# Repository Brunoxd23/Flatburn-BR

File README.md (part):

# FLATBURN: O City Scanner Open-Source (Versão Brasil - Flatburn-BR)

Desenvolvido originalmente no [MIT Senseable City Lab](https://senseable.mit.edu) como parte do projeto [City Scanner](https://senseable.mit.edu/cityscanner/), o **Flatburn** é uma plataforma aberta, modular e movida a energia solar para sensoriamento ambiental urbano instalada em veículos em circulação (ônibus, viaturas, etc.).

Este repositório (**Flatburn-BR**) contém o firmware otimizado, documentação completa em português, esquemáticos de hardware e ferramentas de download de dados para implantação no Brasil.

---

## 📋 Sumário
1. [Especificações Técnicas](#-especificações-técnicas)
2. [Arquitetura do Firmware](#%EF%B8%8F-arquitetura-do-firmware)
3. [Estrutura de Pastas e Módulos](#-estrutura-de-pastas-e-módulos)
4. [Configuração do Ambiente e Ferramentas](#%EF%B8%8F-configuração-do-ambiente-e-ferramentas)
5. [Comandos de Compilação e Gravação (Particle CLI)](#-comandos-de-compilação-e-gravação-particle-cli)
6. [Manual de Comandos do Firmware (CLI Serial / Nuvem)](#-manual-de-comandos-do-firmware-cli-serial--nuvem)
7. [Configurações Principais (cityscanner_config.h)](#-configurações-principais-cityscanner_configh)
8. [Estrutura dos Payloads de Dados](#-estrutura-dos-payloads-de-dados)
9. [Tratamento de Data, Hora e Fuso Horário (Brasília UTC-3)](#-tratamento-de-data-hora-e-fuso-horário-brasília-utc-3)
10. [Histórico de Alterações e Correções de Estabilidade](#%EF%B8%8F-histórico-de-alterações-e-correções-de-estabilidade)

---

## ⚙️ Especificações Técnicas

- **Microcontrolador / Módulo IoT:** Particle B-Series SoM (`b5som` / `bsom`) com suporte a rede celular LTE.
- **Versão do Sistema Operacional:** [Particle Device OS @ 6.3.4](https://docs.particle.io/reference/device-os/firmware/).
- **Linguagem:** C++ (Particle Wiring API).
- **Sensores Embarcados:**
  - **Qualidade do Ar (Material Particulado):** Sensirion SPS30 (PM1.0, PM2.5, PM4, PM10).
  - **Meteorologia:** BME280 (Temperatura, Umidade e Pressão).
  - **Gases:** Sensor eletroquímico via conversor ADC de alta resolução (ADS1256).
  - **Ruído Urbano:** Microfone analógico com amostragem contínua.
  - **Geolocalização:** Módulo GPS com saída NMEA.
  - **Movimento e Detecção de Inatividade:** Acelerômetro / IMU.
  - **Telemetria de Bateria e Solar:** Medidores BQ24195 e LC709203F.
  - **Armazenamento Local:** Módulo MicroSD (buffer redundante quando sem conexão).

---

## 🏛️ Arquitetura do Firmware

O firmware adota um padrão modular de classes Singleton, onde cada classe é responsável por um subsistema do dispositivo:

| Módulo / Classe | Arquivos | Responsabilidade |
| :--- | :--- | :--- |
| **Cityscanner** | `firmware/src/cityscanner.h / .cpp` | Gerenciador central. Controla o loop principal e máquina de estados (`IDLE`, `REALTIME`, `LOGGING`, `PWRSAVE`). |
| **CitySense** | `firmware/src/cityscanner_sense.h / .cpp` | Inicialização, amostragem e conversão de dados de todos os sensores ambientais (SPS30, BME280, ADS1256, Ruído). |
| **CityVitals** | `firmware/src/cityscanner_vitals.h / .cpp` | Aquisição de dados de diagnóstico elétrico: nível de bateria (SOC), tensão, corrente, temperatura e produção de energia dos painéis solares. |
| **CityStore** | `firmware/src/cityscanner_store.h / .cpp` | Manipulação do cartão MicroSD: gravação em buffer CSV, rotação de arquivos e descarga de dados via USB. |
| **LocationService** | `firmware/src/location_service.h / .cpp` | Leitura e parsing de mensagens NMEA do GPS (latitude, longitude, velocidade, altitude e horário Epoch). |
| **MotionService** | `firmware/src/motion_service.h / .cpp` | Monitora o acelerômetro. Se o veículo ficar parado por mais de `INACTIVITY_TIME`, ativa rotinas de economia de energia. |
| **CitySleep** | `firmware/src/cityscanner_sleep.h / .cpp` | Controle de modos de suspensão (`Stop`, `Hibernate`, `Light Sleep`) para evitar descarregar a bateria durante a noite ou estacionado. |
| **CS_core** | Em `cscore` (lib) | Controle dos reguladores de tensão (chaveamento dos barramentos 3.3V e 5V dos sensores). |
| **CLI Handler** | `firmware/src/cityscanner_cli.h` | Interpretador de comandos que recebe instruções via porta Serial (USB) ou pela função de nuvem da Particle. |

---

## 📁 Estrutura de Pastas e Módulos

```text
flartBurn/
├── README.md                  # Documentação principal no GitHub (Português)
├── LICENSE                    # Licença MIT
├── firmware/                  # Código fonte do microcontrolador
│   ├── project.properties     # Configuração básica do projeto Particle
│   ├── README.md              # Documentação técnica do firmware
│   ├── README.pt-BR.md        # Documentação completa em português
│   ├── src/                   # Arquivos-fonte (.cpp e .h)
│   └── lib/                   # Bibliotecas dos sensores e periféricos
├── hardware/                  # Esquemáticos elétricos, PCB (KiCad) e modelos CAD/3D (STEP/STL)
└── documentation/             # Site de documentação Docusaurus e ferramentas (flatburn_downloader.html)
```

---

## 🛠️ Configuração do Ambiente e Ferramentas

Para trabalhar com este firmware, você só precisa do **Node.js** e do **Particle CLI** instalados no computador.

### 1. Instalar o Particle CLI (Global)
No terminal do seu computador (PowerShell ou Prompt de Comando):
```bash
npm install -g particle-cli
```

### 2. Verificar a Instalação
```bash
particle --version
# Exemplo de saída: 3.51.0
```

### 3. Fazer Login na Conta Particle
Para utilizar o compilador na nuvem e os recursos remotos:
```bash
particle login
```
*Insira seu e-mail e senha cadastrados no console da [Particle.io](https://login.particle.io).*

---

## 🚀 Comandos de Compilação e Gravação (Particle CLI)

Todos os comandos abaixo devem ser executados a partir da raiz do repositório (`flartBurn/`):

### 1. Binários Pré-compilados Prontos para Teste
Para facilitar testes imediatos em bancada ou em campo, o projeto dispõe de dois binários prontos:

| Arquivo `.bin` | Configuração Celular | Comportamento do LED | Uso Recomendado |
| :--- | :--- | :--- | :--- |
| **`firmware_sem_celular.bin`** | `CELLULAR_ON_STARTUP FALSE` | ⚪ **Branco suave** (offline) | **Bancada e desenvolvimento local:** Desativa o modem na inicialização, liberando a Serial instantaneamente e gravando dados no MicroSD. |
| **`firmware_com_celular.bin`** | `CELLULAR_ON_STARTUP TRUE` | 🟢 **Verde** $\rightarrow$ 🌐 **Ciano** | **Operação em campo com telemetria:** Conecta à rede móvel e envia dados para a Nuvem Particle. |

---

### 2. Automação com Scripts Rápidos (.bat no Windows)
Você pode executar as ações com 2 cliques ou pelo terminal:

- **Compilação Automática:**
  - `compilar_sem_celular.bat` $\rightarrow$ Ajusta a configuração para `FALSE` e compila `firmware_sem_celular.bin`.
  - `compilar_com_celular.bat` $\rightarrow$ Ajusta a configuração para `TRUE` e compila `firmware_com_celular.bin`.
- **Gravação Direta via USB:**
  - `gravar_sem_celular.bat` $\rightarrow$ Grava a versão offline via USB.
  - `gravar_com_celular.bat` $\rightarrow$ Grava a versão online via USB.

---

### 3. Gravar no Dispositivo via USB (Cabo)
1. Conecte a placa ao computador pelo cabo USB.
2. Coloque a placa em **modo DFU**:
   - Mantenha pressionados os botões **RESET** e **MODE**.
   - Solte o botão **RESET** e continue segurando o botão **MODE** até o LED RGB começar a **piscar rápido em amarelo / âmbar**.
   - Solte o botão **MODE**.
3. Execute o comando de gravação da versão desejada:
   ```bash
   # Opção A: Versão Offline (Recomendada para testes e sem antena celular)
   particle flash --usb firmware_sem_celular.bin

   # Opção B: Versão Online (Conexão celular ativa)
   particle flash --usb firmware_com_celular.bin
   ```

---

### 4. Compilar Manualmente via Terminal
Caso altere o código-fonte manualmente e queira compilar via linha de comando:
```bash
particle compile b5som firmware/ --target 6.3.4 --saveTo firmware.bin
```

---

### 5. Gravar no Dispositivo via Nuvem (OTA - Sem cabo)
Caso o dispositivo esteja na rua ou conectado via celular:
```bash
particle flash NOME_OU_ID_DO_DISPOSITIVO firmware.bin
```

### 6. Visualizar Logs da Porta Serial (Monitor em Tempo Real)
Para acompanhar leituras de sensores e mensagens de debug enviadas pelo dispositivo via USB:
```bash
particle serial monitor --follow
```

### 7. Listar Dispositivos Conectados na USB
```bash
particle serial list
```

### 8. Como Baixar e Unificar o CSV de Dados via Navegador
Para descarregar todos os dados gravados no cartão MicroSD e gerar uma planilha única `.csv` com georreferenciamento e timestamps corrigidos:

1. **Liberar a porta USB:**  
   Se o comando `particle serial monitor` estiver rodando no terminal, feche-o pressionando **`Ctrl + C`** *(no Windows, a porta serial fica bloqueada caso outro programa esteja usando)*.
2. **Abrir a ferramenta web:**  
   Abra o arquivo [`documentation/content/explore/flatburn_downloader.html`](documentation/content/explore/flatburn_downloader.html) no **Google Chrome** ou **Microsoft Edge** (estes navegadores possuem suporte nativo à *Web Serial API*).
3. **Conectar ao dispositivo:**  
   Na página aberta, clique em **Connect** e selecione a porta serial do Flatburn (geralmente identificada como **"B-SoM CDC Mode"** ou **"USB Serial Device"**).
4. **Baixar e Unificar:**  
   Clique no botão **"Download All, Parse & Merge"**. O sistema baixa todos os blocos do SD, limpa os dados e unifica tudo em uma única tabela.
5. **Salvar o arquivo:**  
   Clique em **"Save CSV File"** para salvar a planilha `.csv` final na sua pasta de Downloads.

### 9. Significado dos LEDs de Status (Guia de Cores)
O módulo Particle e a placa Flatburn utilizam LEDs indicadores para sinalizar o estado do hardware e das conexões:

| Cor do LED | Padrão | Significado | O que fazer / Situação |
| :--- | :--- | :--- | :--- |
| 🟢 **Verde** | Piscando rápido | **Buscando Rede Celular:** O modem celular está ativo e tentando se registrar na torre de telefonia. | Comportamento normal logo após ligar a placa ou gravar novo firmware. |
| 🔵 **Azul Escuro** | Piscando | **Modo de Escuta (Listening Mode):** Placa aguardando comandos USB ou sistema desatualizado (firmware do Flatburn pausado). | 1. Dê 1 clique no botão **RESET**.<br>2. Se continuar azul ou for placa nova, coloque em DFU (amarelo) e execute `particle update`. |
| 🌐 **Ciano (Azul Claro)** | Piscando rápido | **Conectando à Nuvem:** Autenticando com os servidores da Particle após conectar na torre celular. | Aguardar alguns segundos até a conclusão do handshake. |
| 🌐 **Ciano (Azul Claro)** | Pulsando suave ("respirando") | **Conectado e Online:** Comunicação ativa e estável com a Nuvem Particle. | Dispositivo 100% online e apto a transmitir dados em tempo real. |
| 🟡 **Amarelo / Âmbar** | Piscando rápido | **Modo DFU:** Placa pronta para receber novo firmware via USB (`particle flash --usb`). | Gravar o firmware pelo terminal ou pressionar RESET para sair. |
| ⚪ **Branco** | Pulsando suave | **Modo Offline:** Modem celular desligado (`Cellular.off()`), gravando dados apenas localmente no SD Card. | Padrão do Flatburn para economia de energia durante coletas. |
| 🟣 **Magenta / Roxo** | Piscando rápido | **Safe Mode / Atualização OTA:** Atualizando firmware pela nuvem ou em modo de proteção. | Aguardar o término do download/gravação. |
| 🔴 **Vermelho** *(Placa Flatburn)* | Piscando lento / Aceso | **Carga / Sistema Ativo:** LED do circuito de alimentação (BQ25798) e amostragem ativa dos sensores. | Normal durante a operação e quando conectado ao cabo USB. |

> [!TIP]
> **Placa travada piscando em Azul Escuro (Listening Mode) ou não inicializa após gravar?**  
> Isso é muito comum em placas novas ou virgens de fábrica cujo sistema operacional interno (*Device OS*) ainda está em versões antigas:
> 1. Feche o monitor serial com `Ctrl + C` para liberar a porta USB.
> 2. Coloque a placa em **modo DFU** (LED piscando rápido em **amarelo**): segure `RESET + MODE`, solte `RESET`, espere piscar em amarelo e solte `MODE`.
> 3. No terminal, execute a atualização do sistema:
>    ```bash
>    particle update
>    ```
> 4. Após a conclusão com sucesso, regrave o firmware desejado (`particle flash --usb firmware_sem_celular.bin` ou use o script `.bat`).

---

## 🎮 Manual de Comandos do Firmware (CLI Serial / Nuvem)

O firmware possui um interpretador de comandos integrado (`cityscanner_cli.h`).  
Os comandos podem ser enviados de duas formas:
1. **Pela porta Serial USB:** digitando diretamente no monitor serial ou enviando via scripts em Python.
2. **Pela Nuvem da Particle:** chamando a função `CLI` da placa pelo terminal:
   ```bash
   particle call NOME_DO_DISPOSITIVO CLI "COMANDO"
   ```

Abaixo está a lista completa de comandos suportados:

### A. Download e Gerenciamento do Cartão SD
| Comando | Descrição |
| :--- | :--- |
| `LIST` | Lista todos os arquivos `.csv` armazenados no cartão MicroSD. |
| `READ:<nome_arquivo>` | Imprime na Serial todo o conteúdo do arquivo especificado (ex: `READ:0001.csv`). |
| `DELETE_ALL` | Remove do cartão SD os arquivos que já foram baixados. |
| `sd,dump,all` | Despeja todos os arquivos de dados na porta Serial. |
| `sd,dump,<N>` | Despeja os últimos `<N>` arquivos de dados (ex: `sd,dump,5`). |
| `sd,files` | Retorna a quantidade de arquivos de dados pendentes no cartão SD. |
| `sd,health` | Retorna o status de saúde e conectividade do cartão SD. |
| `sd,reinit` | Reinicializa o driver do cartão SD caso ocorra alguma falha. |
| `sd,format` | Formata e reinicia a estrutura de pastas do cartão SD. |

### B. Leituras Imediatas e Sensores
| Comando | Descrição |
| :--- | :--- |
| `last,payload` | Retorna a última leitura completa dos sensores (GPS + Poluentes + Clima). |
| `last,vitals` | Retorna a última leitura de telemetria elétrica (Bateria + Solar). |
| `device-check` | Executa um teste em todos os sensores e retorna a linha consolidada. |
| `location` | Retorna as coordenadas GPS atuais (`latitude,longitude`). |
| `battery` | Retorna status detalhado da bateria (SOC %, tensão, corrente de carga). |
| `solar` ou `input` | Retorna a tensão e corrente produzidas pelos painéis solares. |
| `opc` | Retorna os dados brutos da última leitura do sensor de material particulado SPS30. |

### C. Controle de Energia dos Sensores (Chaveamento de Barramentos)
| Comando | Descrição |
| :--- | :--- |
| `3v3on` | Liga a alimentação de 3.3V e inicializa GPS, temperatura, ruído e gás. |
| `3v3off` | Desliga todos os sensores de 3.3V para economizar energia. |
| `5von` | Liga a linha de 5V (alimentação necessária para o sensor SPS30). |
| `5voff` | Desliga a linha de 5V e desativa o sensor SPS30. |
| `opcon` | Liga o sensor de partículas SPS30. |
| `opcoff` | Desliga o sensor de partículas SPS30. |
| `autosleep,on` | Habilita o modo de suspensão automática quando o veículo estaciona. |
| `autosleep,off` | Força o dispositivo a ficar acordado mesmo se estiver parado. |

### D. Controle do Sistema e Modos de Espera
| Comando | Descrição |
| :--- | :--- |
| `reboot` | Reinicia o microcontrolador imediatamente (`System.reset()`). |
| `dfu` | Coloca a placa em modo DFU remotamente para receber novo firmware. |
| `stop` | Coloca a placa em modo de espera profundo (Stop Sleep) por até 12 horas ou até movimento. |
| `hibernate,<tempo>,<unidade>` | Coloca a placa em hibernação profunda por um tempo pré-determinado.<br>Exemplo: `hibernate,30,minutes` ou `hibernate,2,hours`. |

---

## ⚙️ Configurações Principais (`cityscanner_config.h`)

Para alterar a frequência de coleta, modos de operação ou limites de segurança de bateria, edite o arquivo [firmware/src/cityscanner_config.h](firmware/src/cityscanner_config.h):

| Parâmetro | Padrão | O que configura |
| :--- | :--- | :--- |
| `MODE` | `LOGGING` | Modo padrão de operação (`REALTIME`, `LOGGING` ou `PWRSAVE`). |
| `SAMPLE_RATE` | `5` | Intervalo em segundos entre amostragens de sensores de qualidade do ar. |
| `VITALS_RATE` | `300` | Intervalo em segundos (5 minutos) entre leituras de telemetria da bateria/solar. |
| `INACTIVITY_TIME`| `120` | Segundos sem movimento do veículo para ativar o modo de economia. |
| `AUTOSLEEP` | `TRUE` | Ativa/desativa se a placa dorme automaticamente quando estacionada. |
| `LOW_BATTERY_THRESHOLD` | `3.70` | Tensão em Volts da bateria para acionar o alerta de bateria baixa. |
| `RECORDS_PER_FILE` | `200` | Quantidade de registros por arquivo `.csv` no cartão SD antes de rotacionar. |
| `CELLULAR_ON_STARTUP` | `FALSE` | Define se a conexão celular é ligada imediatamente ao dar boot. |
| `TIMEZONE_OFFSET` | `-3` | Fuso horário em horas (padrão `-3` para Horário de Brasília / São Paulo). |

---

## 📊 Estrutura dos Payloads de Dados

Os dados gravados no cartão SD e transmitidos via nuvem/USB seguem o padrão CSV delimitado por vírgulas:

### 1. Payload de Sensores (Ambiental)
```text
deviceID, timestamp, latitude, longitude, PM1.0, PM2.5, PM4, PM10, numPM0.5, numPM1, numPM2.5, numPM4, numPM10, PM_size, temperature, humidity, gas_op1_w, gas_op1_r, gas_op2_w, gas_op2_r, noise
```

### 2. Payload de Vitals (Diagnóstico Elétrico)
```text
deviceID, time, latitude, longitude, SOC_batt, temp_batt, voltage_batt, voltage_particle, current_batt, isCharging, isCharginS, temp_int, hum_int, voltage_solar, current_solar, cell_strength
```

---

## 🕒 Tratamento de Data, Hora e Fuso Horário (Brasília UTC-3)

Para garantir precisão nas análises em **São Paulo / Brasil**, o firmware conta com as seguintes regras de sincronização temporal e georreferenciamento:

### 1. Correção do Timestamp Epoch
- O cálculo da data do GPS utiliza `CalendarYrToTm(tinyGps->date.year())`, convertendo o ano civil de 4 dígitos (ex.: 2024, 2026) diretamente em anos transcorridos desde 1970.
- Isso gera um **Unix Epoch UTC padronizado em segundos** na coluna `timestamp` do CSV, pronto para ser lido pelo downloader web ou bibliotecas de análise (ex.: Pandas).

### 2. Sincronização Automática do Relógio Interno (RTC)
- Assim que o módulo GPS obtém uma data e hora válidas dos satélites (`tinyGps->date.isValid()` e ano >= 2020), o firmware executa `Time.setTime(epoch)`.

### 3. Fuso Horário de Brasília (`TIMEZONE_OFFSET -3`)
- O parâmetro `#define TIMEZONE_OFFSET -3` no [cityscanner_config.h](firmware/src/cityscanner_config.h) ativa a compensação local via `Time.zone(-3)`. Os arquivos no SD são nomeados como `MMDDHHMM.csv` em horário de Brasília.

---

## 🛠️ Histórico de Alterações e Correções de Estabilidade

1. **Taxa de Transmissão Serial Atualizada para 115200 Baud:**
   - A inicialização da porta Serial em [main.cpp](firmware/src/main.cpp) foi ajustada de `9600` para `115200` baud. Isso sincronizou a velocidade do microcontrolador com a interface web ([flatburn_downloader.html](documentation/content/explore/flatburn_downloader.html)), permitindo o download ultrarrápido dos arquivos do cartão SD via USB.

2. **Timeout de Proteção no Conversor ADC ADS1256:**
   - Adicionada verificação com timeout de 100ms nas funções `waitForLowDRDY()` e `waitForHighDRDY()` no driver do sensor de gás ADS1256 ([ADS1256.cpp](firmware/lib/ADS1256-main/src/ADS1256.cpp)). Evita travamentos caso o sensor esteja ausente ou o pino DRDY em nível alto.

3. **Correção na Ordem de Energização das Linhas 3.3V e 5V:**
   - Em [cityscanner.cpp](firmware/src/cityscanner.cpp), a inicialização dos barramentos de alimentação (`core.enable3V3(true)` e `core.enable5V(true)`) foi movida para o **início da função `init()`**, garantindo energia no barramento I2C e SD Card antes do acesso.

4. **Desativação de Sketches de Exemplo nas Bibliotecas (`.ino.bak`):**
   - Todos os arquivos `.ino` situados dentro da pasta `lib/` (ex.: `ADS1256-Example.ino`) foram renomeados para `.ino.bak`. Evita que o compilador da Particle inclua sketches de teste de bibliotecas no binário final (~80 KB).

5. **Exibição do Modo `LOGGING` em Tempo Real na Serial:**
   - Ativada a chamada da função `printDebug()` no bloco `case LOGGING:` dentro do `loop()`, imprimindo a tabela consolidada de todos os sensores diretamente no monitor serial a cada 5 segundos.

6. **Desativação Total do Modem Celular no Boot:**
   - Incluído o comando `Cellular.off()` no bloco `STARTUP()` de [main.cpp](firmware/src/main.cpp) para eliminar a busca por torres e o LED piscando em verde.

7. **Correção do Pino CS e Barramento SPI1 do Conversor ADC de Gases (ADS1256):**
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
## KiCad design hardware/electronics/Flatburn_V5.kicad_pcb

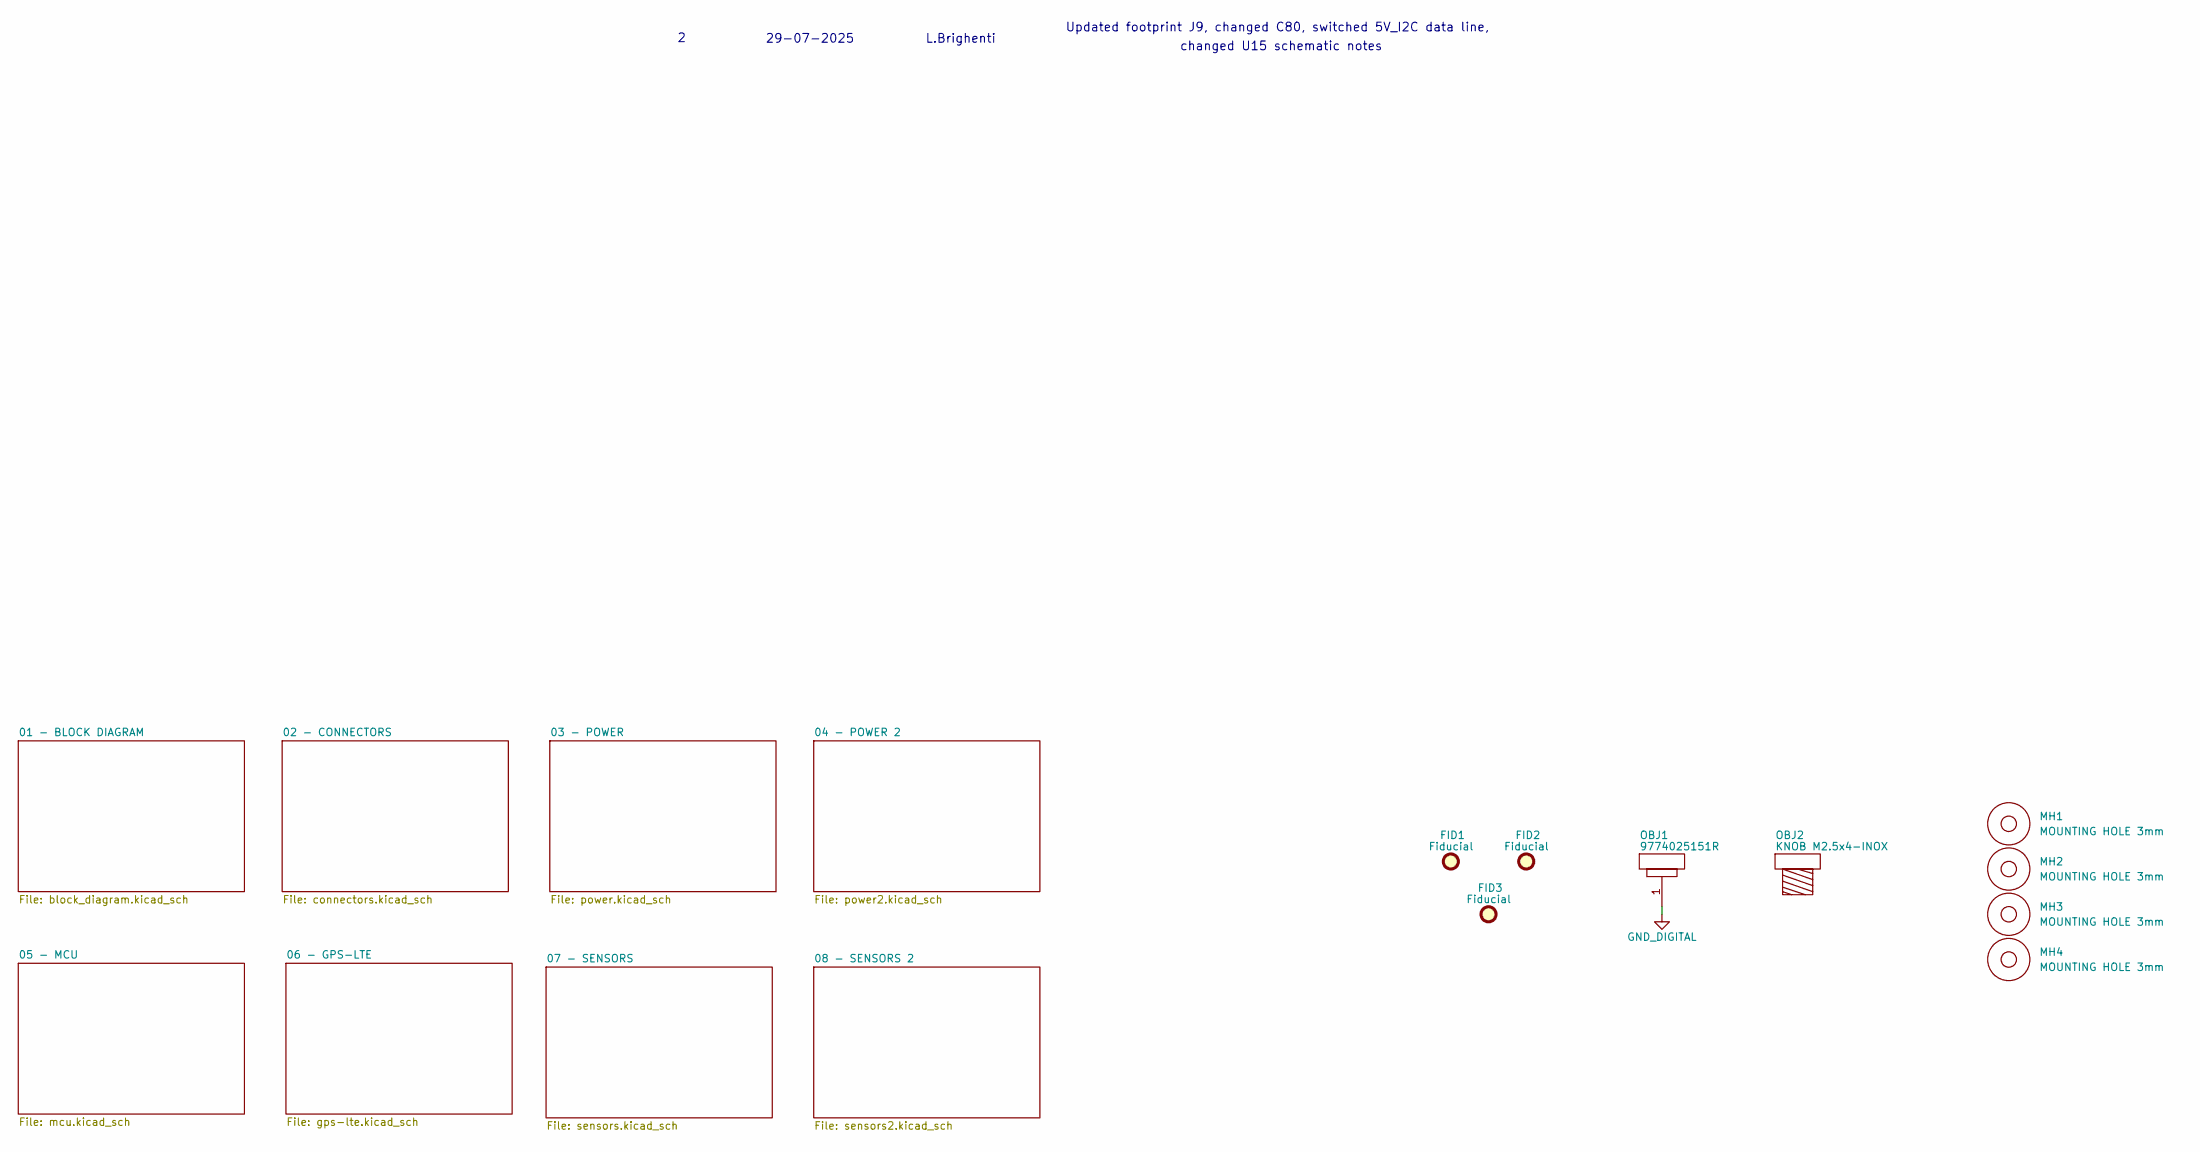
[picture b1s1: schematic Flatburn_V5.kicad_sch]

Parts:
FID1, FID2, FID3: Fiducial; Fiducial_1mm_Mask3mm
MH1, MH2, MH3, MH4: MOUNTING HOLE 3mm
OBJ1: 9774025151R; SPACER M2.5 - 9774025151R; MPN 9774025151R
OBJ2: KNOB M2.5x4-INOX

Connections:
GND_DIGITAL: OBJ1.1; also elsewhere on the board

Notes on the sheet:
L.Brighenti
Updated footprint J9, changed C80, switched 5V_I2C data line,
29-07-2025
changed U15 schematic notes

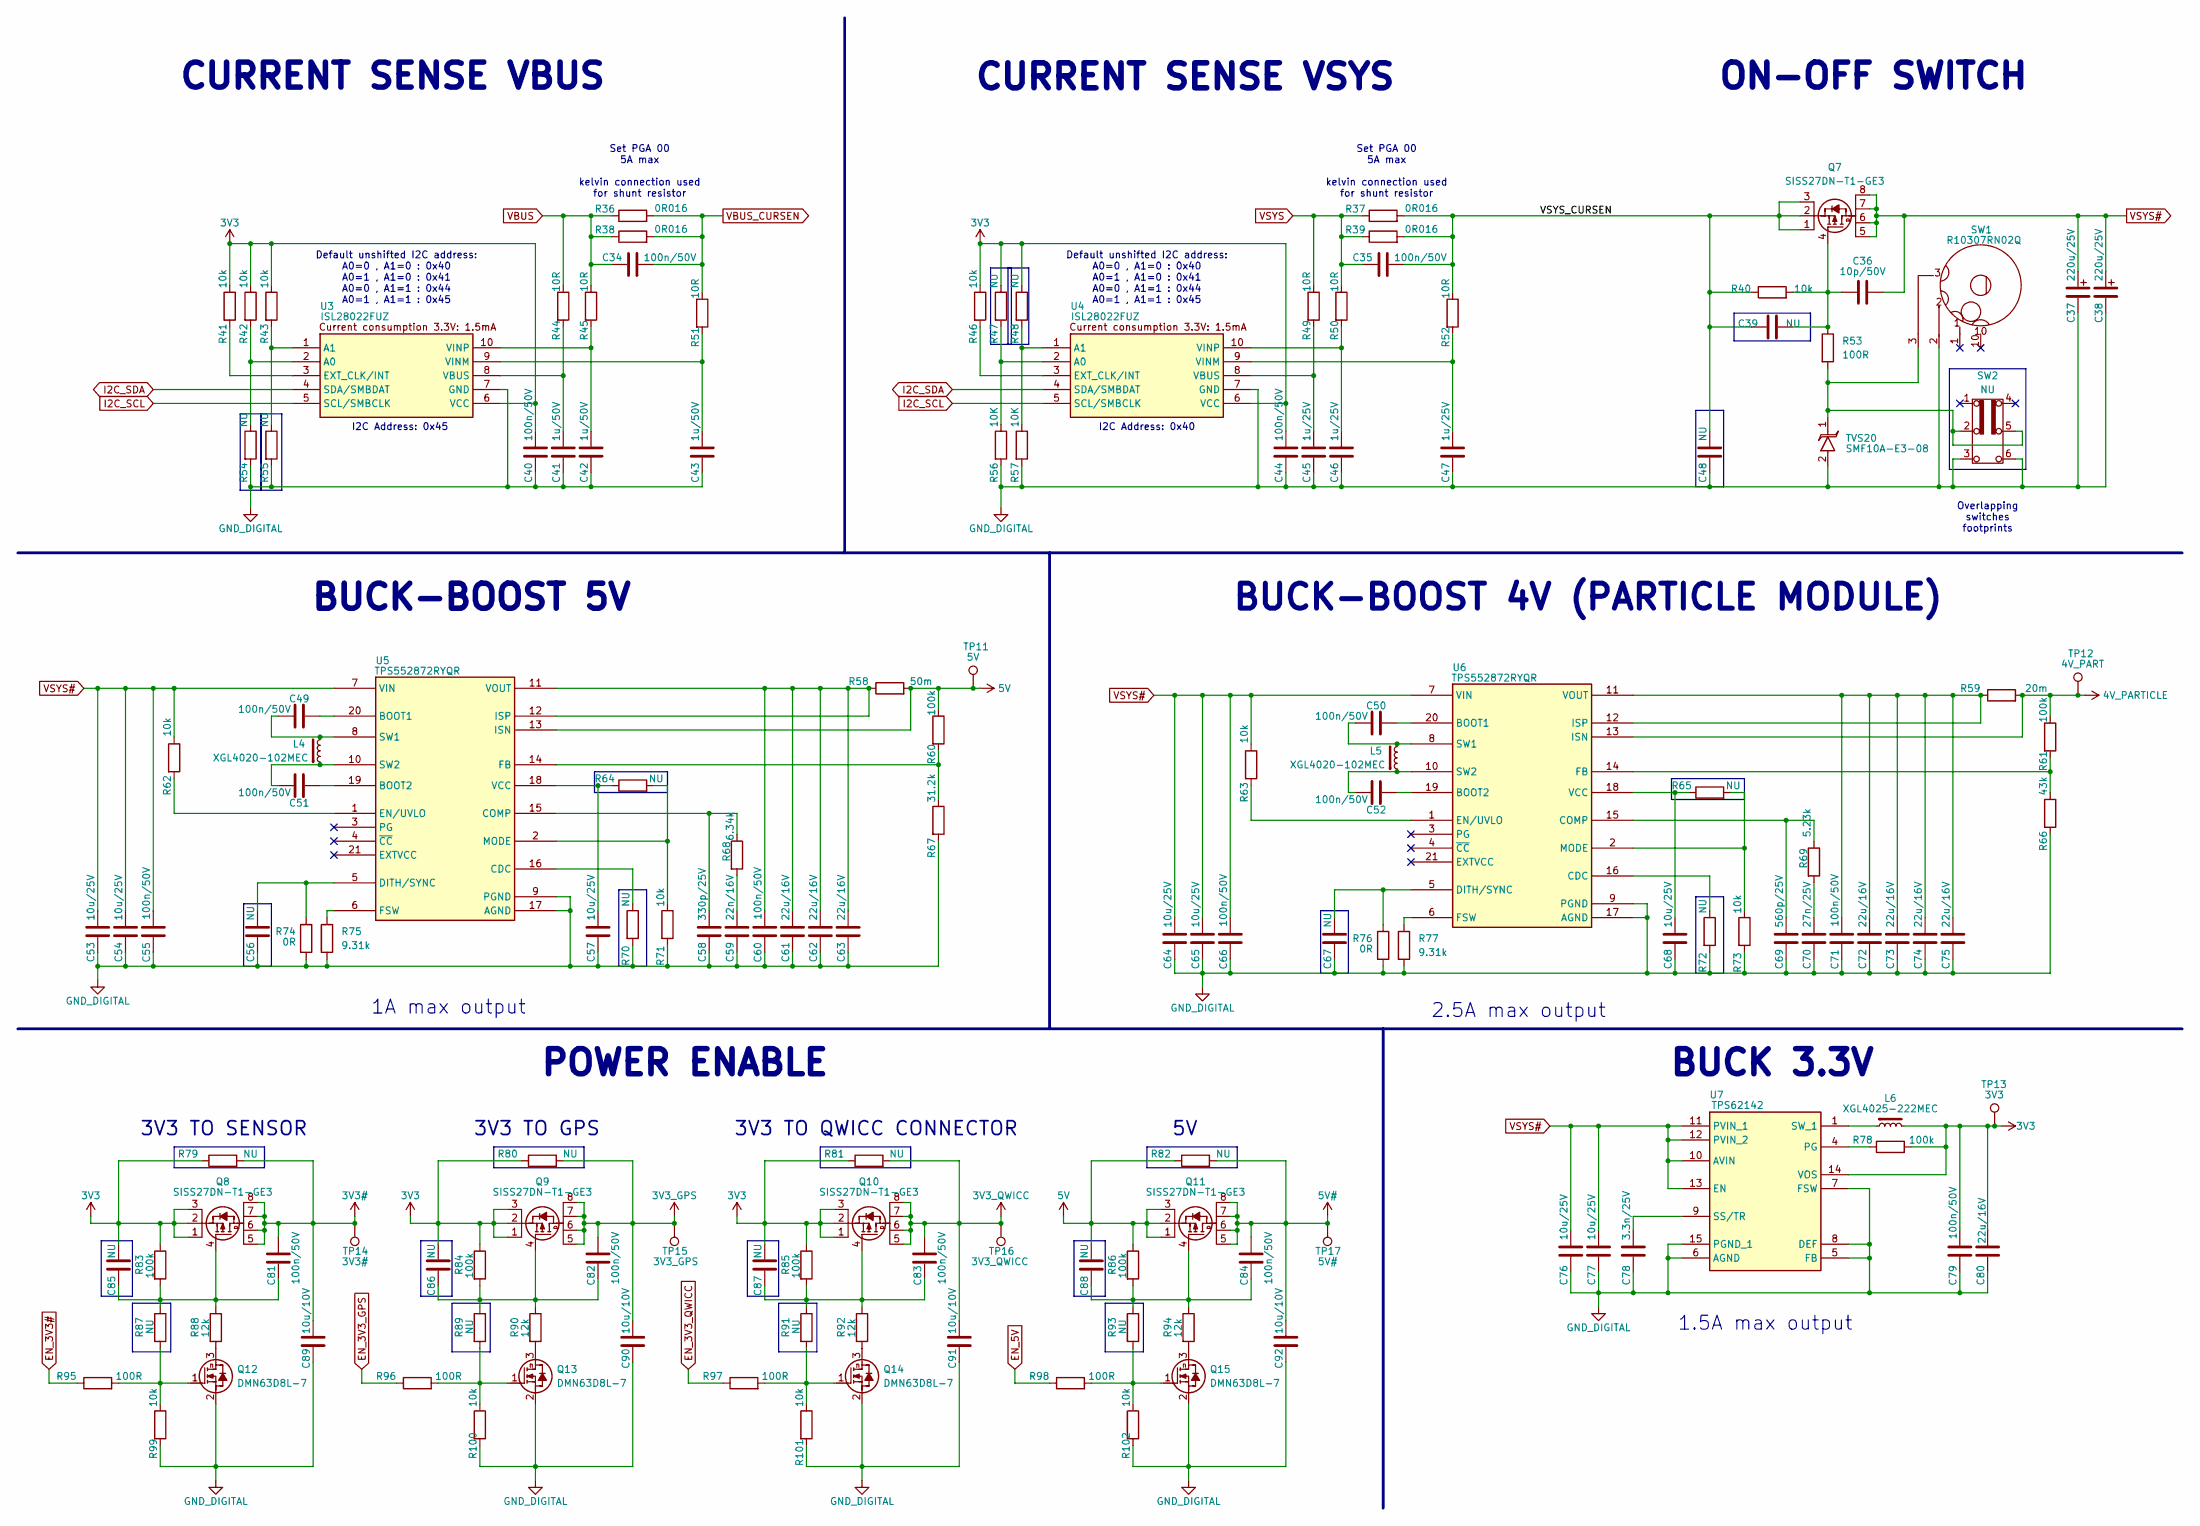
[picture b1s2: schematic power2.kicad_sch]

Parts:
C34, C35, C40, C44, C49, C50, C51, C52, C55, C60, C66, C71, C79, C81, C82, C83, C84: 100n/50V; C_0402_1005Metric
C36: 10p/50V; C_0402_1005Metric; MPN GCM1555C1H100JA16D
C37, C38: 220u/25V; CP_Elec_6.3x7.7; MPN UCM1E221MCL1GS
C39, C48, C85, C86, C87, C88: NU; C_0402_1005Metric
C41, C42, C43: 1u/50V; C_0805_2012Metric
C45, C46, C47: 1u/25V; C_0603_1608Metric; MPN CL10B105KA8NNNC
C53, C54, C57, C64, C65, C68, C76, C77: 10u/25V; C_0603_1608Metric; MPN GRM188R61E106KA73D
C56, C67: NU; C_0603_1608Metric; MPN GRM188R61E106KA73D
C58: 330p/25V; C_0603_1608Metric; MPN C0603C331J3HACAUTO
C59: 22n/16V; C_0603_1608Metric; MPN 0603YC223J4T2A
C61, C62, C63, C72, C73, C74, C75: 22u/16V; C_0805_2012Metric; MPN GRM21BC81C226ME44L
C69: 560p/25V; C_0603_1608Metric; MPN GRM1885C1E561JA01D
C70: 27n/25V; C_0603_1608Metric; MPN C0603C273J3RACAUTO
C78: 3.3n/25V; C_0402_1005Metric; MPN 885012205047
C80: 22u/16V; C_0603_1608Metric; MPN KGM15CR51C226MT
C89, C90, C91, C92: 10u/10V; C_0603_1608Metric
L4, L5: XGL4020-102MEC; L_Coilcraft_XxL4020; MPN XGL4020-102MEC
L6: XGL4025-222MEC; L_Coilcraft_XxL4020; MPN XGL4025-222MEC
Q7, Q8, Q9, Q10, Q11: SISS27DN-T1-GE3; PowerPAK 121-8; MPN SISS27DN-T1-GE3
Q12, Q13, Q14, Q15: DMN63D8L-7; SOT-23; MPN DMN63D8L-7
R36, R37, R38, R39: 0R016; R_1206_3216Metric; MPN RL1206FR-070R016L
R40, R41, R42, R43, R46, R62, R63, R71, R73, R99, R100, R101, R102: 10k; R_0402_1005Metric
R44, R45, R49, R50, R51, R52: 10R; R_0603_1608Metric
R47, R48, R54, R55, R64, R65, R70, R72: NU; R_0402_1005Metric
R53, R95, R96, R97, R98: 100R; R_0402_1005Metric
R56, R57: 10K; R_0402_1005Metric
R58: 50m; R_0603_1608Metric; MPN PE0603FRF570R05L
R59: 20m; R_0603_1608Metric; MPN CFN0603-FZ-R020ELF
R60, R61, R78, R83, R84, R85, R86: 100k; R_0402_1005Metric
R66: 43k; R_0402_1005Metric; MPN RC0402FR-0743KL
R67: 31.2k; R_0402_1005Metric; MPN RN73H1ETTP3122D25
R68: 6.34k; R_0603_1608Metric; MPN RR0816P-6341-D-78H
R69: 5.23k; R_0603_1608Metric; MPN CPF0603F5K23C1
R74, R76: 0R; R_0402_1005Metric; MPN RCS04020000Z0ED
R75, R77: 9.31k; R_0402_1005Metric; MPN RC0402FR-079K31L
R79, R80, R81, R82: NU; R_1206_3216Metric; MPN RCA12060000ZSEA
R87, R89, R91, R93: NU; R_0402_1005Metric; MPN RCS04020000Z0ED
R88, R90, R92, R94: 12k; R_0402_1005Metric
SW1: R10307RN02Q; MPN R10307RN02Q
SW2: NU; FS22ABP; MPN FS22ABP
TP11: 5V; TestPoint_Pad_D1.0mm
TP12: 4V_PART; TestPoint_Pad_D1.0mm
TP13: 3V3; TestPoint_Pad_D1.0mm
TP14: 3V3#; TestPoint_Pad_D1.0mm
TP15: 3V3_GPS; TestPoint_Pad_D1.0mm
TP16: 3V3_QWICC; TestPoint_Pad_D1.0mm
TP17: 5V#; TestPoint_Pad_D1.0mm
TVS20: SMF10A-E3-08; D_SMF; MPN SMF10A-E3-08
U3, U4: ISL28022FUZ; SOP50P490X110-10N; MPN ISL28022FUZ
U5, U6: TPS552872RYQR; TPS552892QWRYQRQ1; MPN TPS630702RNMR
U7: TPS62142; QFN50P300X300X100-17N-D; MPN TPS62142RGTT

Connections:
3V3: C40.1, C44.1, C79.2, C80.1, C85.2, C86.2, C87.2, L6.1, Q8.1 (S), Q8.2 (S), Q8.3 (S), Q9.1 (S), Q9.2 (S), Q9.3 (S), Q10.1 (S), Q10.2 (S), Q10.3 (S), R41.1, R42.1, R43.1, R46.1, R47.1, R48.1, R78.2, R79.1, R80.1, R81.1, R83.1, R84.1, R85.1, TP13.1, U3.6 (VCC), U4.6 (VCC), U7.14 (VOS); also elsewhere on the board
3V3#: C81.2, C89.1, Q8.5 (D), Q8.6 (D), Q8.7 (D), Q8.8 (D), Q8.9 (D), R79.2, TP14.1; also elsewhere on the board
3V3_GPS: C82.2, C90.1, Q9.5 (D), Q9.6 (D), Q9.7 (D), Q9.8 (D), Q9.9 (D), R80.2, TP15.1; also elsewhere on the board
3V3_QWICC: C83.2, C91.1, Q10.5 (D), Q10.6 (D), Q10.7 (D), Q10.8 (D), Q10.9 (D), R81.2, TP16.1; also elsewhere on the board
4V_PARTICLE: R59.2, R61.1, TP12.1, U6.13 (ISN); also elsewhere on the board
5V: C88.2, Q11.1 (S), Q11.2 (S), Q11.3 (S), R58.2, R60.1, R82.1, R86.1, TP11.1, U5.13 (ISN); also elsewhere on the board
5V#: C84.2, C92.1, Q11.5 (D), Q11.6 (D), Q11.7 (D), Q11.8 (D), Q11.9 (D), R82.2, TP17.1; also elsewhere on the board
/04 - POWER 2/VSYS_CURSEN: C35.1, C39.1, C48.1, Q7.1 (S), Q7.2 (S), Q7.3 (S), R37.2, R39.2, R40.1, R52.1
EN_3V3#: R95.1; also elsewhere on the board
EN_3V3_GPS: R96.1; also elsewhere on the board
EN_3V3_QWICC: R97.1; also elsewhere on the board
EN_5V: R98.1; also elsewhere on the board
GND_DIGITAL: C37.2, C38.2, C40.2, C41.2, C42.2, C43.2, C44.2, C45.2, C46.2, C47.2, C48.2, C53.2, C54.2, C55.1, C56.2, C57.2, C58.2, C59.2, C60.1, C61.2, C62.2, C63.2, C64.2, C65.2, C66.1, C67.2, C68.2, C69.2, C70.2, C71.1, C72.2, C73.2, C74.2, C75.2, C76.2, C77.2, C78.2, C79.1, C80.2, C89.2, C90.2, C91.2, C92.2, Q12.2 (S), Q13.2 (S), Q14.2 (S), Q15.2 (S), R54.2, R55.2, R56.2, R57.2, R66.2, R67.2, R70.2, R71.2, R72.2, R73.2, R74.2, R75.2, R76.2, R77.2, R99.2, R100.2, R101.2, R102.2, SW1.2, SW2.3 (B1), SW2.6 (B2), TVS20.2, U3.7 (GND), U4.7 (GND), U5.9 (PGND), U5.17 (AGND), U6.9 (PGND), U6.17 (AGND), U7.5 (FB), U7.6 (AGND), U7.7 (FSW), U7.8 (DEF), U7.15 (PGND_1), U7.16 (PGND_2); also elsewhere on the board
I2C_SCL: U3.5 (SCL/SMBCLK), U4.5 (SCL/SMBCLK); also elsewhere on the board
I2C_SDA: U3.4 (SDA/SMBDAT), U4.4 (SDA/SMBDAT); also elsewhere on the board
unnamed: C59.1, R68.2
unnamed: C70.1, R69.2
unnamed: C36.1, C39.2, Q7.4 (G), R40.2, R53.1
unnamed: C81.1, C85.1, Q8.4 (G), R83.2, R87.1, R88.1
unnamed: C82.1, C86.1, Q9.4 (G), R84.2, R89.1, R90.1
unnamed: C83.1, C87.1, Q10.4 (G), R85.2, R91.1, R92.1
unnamed: C84.1, C88.1, Q11.4 (G), R86.2, R93.1, R94.1
unnamed: Q12.3 (D), R88.2
unnamed: Q12.1 (G), R87.2, R95.2, R99.1
unnamed: Q13.3 (D), R90.2
unnamed: Q13.1 (G), R89.2, R96.2, R100.1
unnamed: Q14.3 (D), R92.2
unnamed: Q14.1 (G), R91.2, R97.2, R101.1
unnamed: Q15.3 (D), R94.2
unnamed: Q15.1 (G), R93.2, R98.2, R102.1
unnamed: R53.2, SW1.3, SW2.2 (COM), SW2.5 (COM), TVS20.1
unnamed: R42.2, R54.1, U3.2 (A0)
unnamed: R43.2, R55.1, U3.1 (A1)
unnamed: R41.2, U3.3 (EXT_CLK/INT)
unnamed: C41.1, R44.2, U3.8 (VBUS)
unnamed: C43.1, R51.2, U3.9 (VINM)
unnamed: C42.1, R45.2, U3.10 (VINP)
unnamed: R47.2, R56.1, U4.2 (A0)
unnamed: R48.2, R57.1, U4.1 (A1)
unnamed: R46.2, U4.3 (EXT_CLK/INT)
unnamed: C45.1, R49.2, U4.8 (VBUS)
unnamed: C47.1, R52.2, U4.9 (VINM)
unnamed: C46.1, R50.2, U4.10 (VINP)
unnamed: C49.2, U5.20 (BOOT1)
unnamed: C51.2, U5.19 (BOOT2)
unnamed: R70.1, U5.16 (CDC)
unnamed: C58.1, R68.1, U5.15 (COMP)
unnamed: C56.1, R74.1, U5.5 (DITH/SYNC)
unnamed: R62.2, U5.1 (EN/UVLO)
unnamed: R60.2, R67.1, U5.14 (FB)
unnamed: R75.1, U5.6 (FSW)
unnamed: C60.2, C61.1, C62.1, C63.1, R58.1, U5.11 (VOUT), U5.12 (ISP)
unnamed: R64.2, R71.1, U5.2 (MODE)
unnamed: C49.1, L4.1, U5.8 (SW1)
unnamed: C51.1, L4.2, U5.10 (SW2)
unnamed: C57.1, R64.1, U5.18 (VCC)
unnamed: C50.2, U6.20 (BOOT1)
unnamed: C52.2, U6.19 (BOOT2)
unnamed: R72.1, U6.16 (CDC)
unnamed: C69.1, R69.1, U6.15 (COMP)
unnamed: C67.1, R76.1, U6.5 (DITH/SYNC)
unnamed: R63.2, U6.1 (EN/UVLO)
unnamed: R61.2, R66.1, U6.14 (FB)
unnamed: R77.1, U6.6 (FSW)
unnamed: C71.2, C72.1, C73.1, C74.1, C75.1, R59.1, U6.11 (VOUT), U6.12 (ISP)
unnamed: R65.2, R73.1, U6.2 (MODE)
unnamed: C50.1, L5.1, U6.8 (SW1)
unnamed: C52.1, L5.2, U6.10 (SW2)
unnamed: C68.1, R65.1, U6.18 (VCC)
unnamed: R78.1, U7.4 (PG)
unnamed: C78.1, U7.9 (SS/TR)
unnamed: L6.2, U7.1 (SW_1), U7.2 (SW_2), U7.3 (SW_3)
VBUS: C34.2, R36.1, R38.1, R44.1, R45.1; also elsewhere on the board
VBUS_CURSEN: C34.1, R36.2, R38.2, R51.1; also elsewhere on the board
VSYS: C35.2, R37.1, R39.1, R49.1, R50.1; also elsewhere on the board
VSYS#: C36.2, C37.1, C38.1, C53.1, C54.1, C55.2, C64.1, C65.1, C66.2, C76.1, C77.1, Q7.5 (D), Q7.6 (D), Q7.7 (D), Q7.8 (D), Q7.9 (D), R62.1, R63.1, U5.7 (VIN), U6.7 (VIN), U7.10 (AVIN), U7.11 (PVIN_1), U7.12 (PVIN_2), U7.13 (EN)

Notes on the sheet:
I2C Address: 0x40
CURRENT SENSE VBUS
1A max output
1.5A max output
BUCK-BOOST 5V
3V3 TO GPS
POWER ENABLE
Default unshifted I2C address: A0=0 , A1=0 : 0x40 A0=1 , A1=0 : 0x41 A0=0 , A1=1 : 0x44 A0=1 , A1=1 : 0x45
BUCK-BOOST 4V (PARTICLE MODULE)
I2C Address: 0x45
ON-OFF SWITCH
3V3 TO QWICC CONNECTOR
3V3 TO SENSOR
CURRENT SENSE VSYS
Set PGA 00 5A max kelvin connection used for shunt resistor
Overlapping switches footprints
BUCK 3.3V
2.5A max output

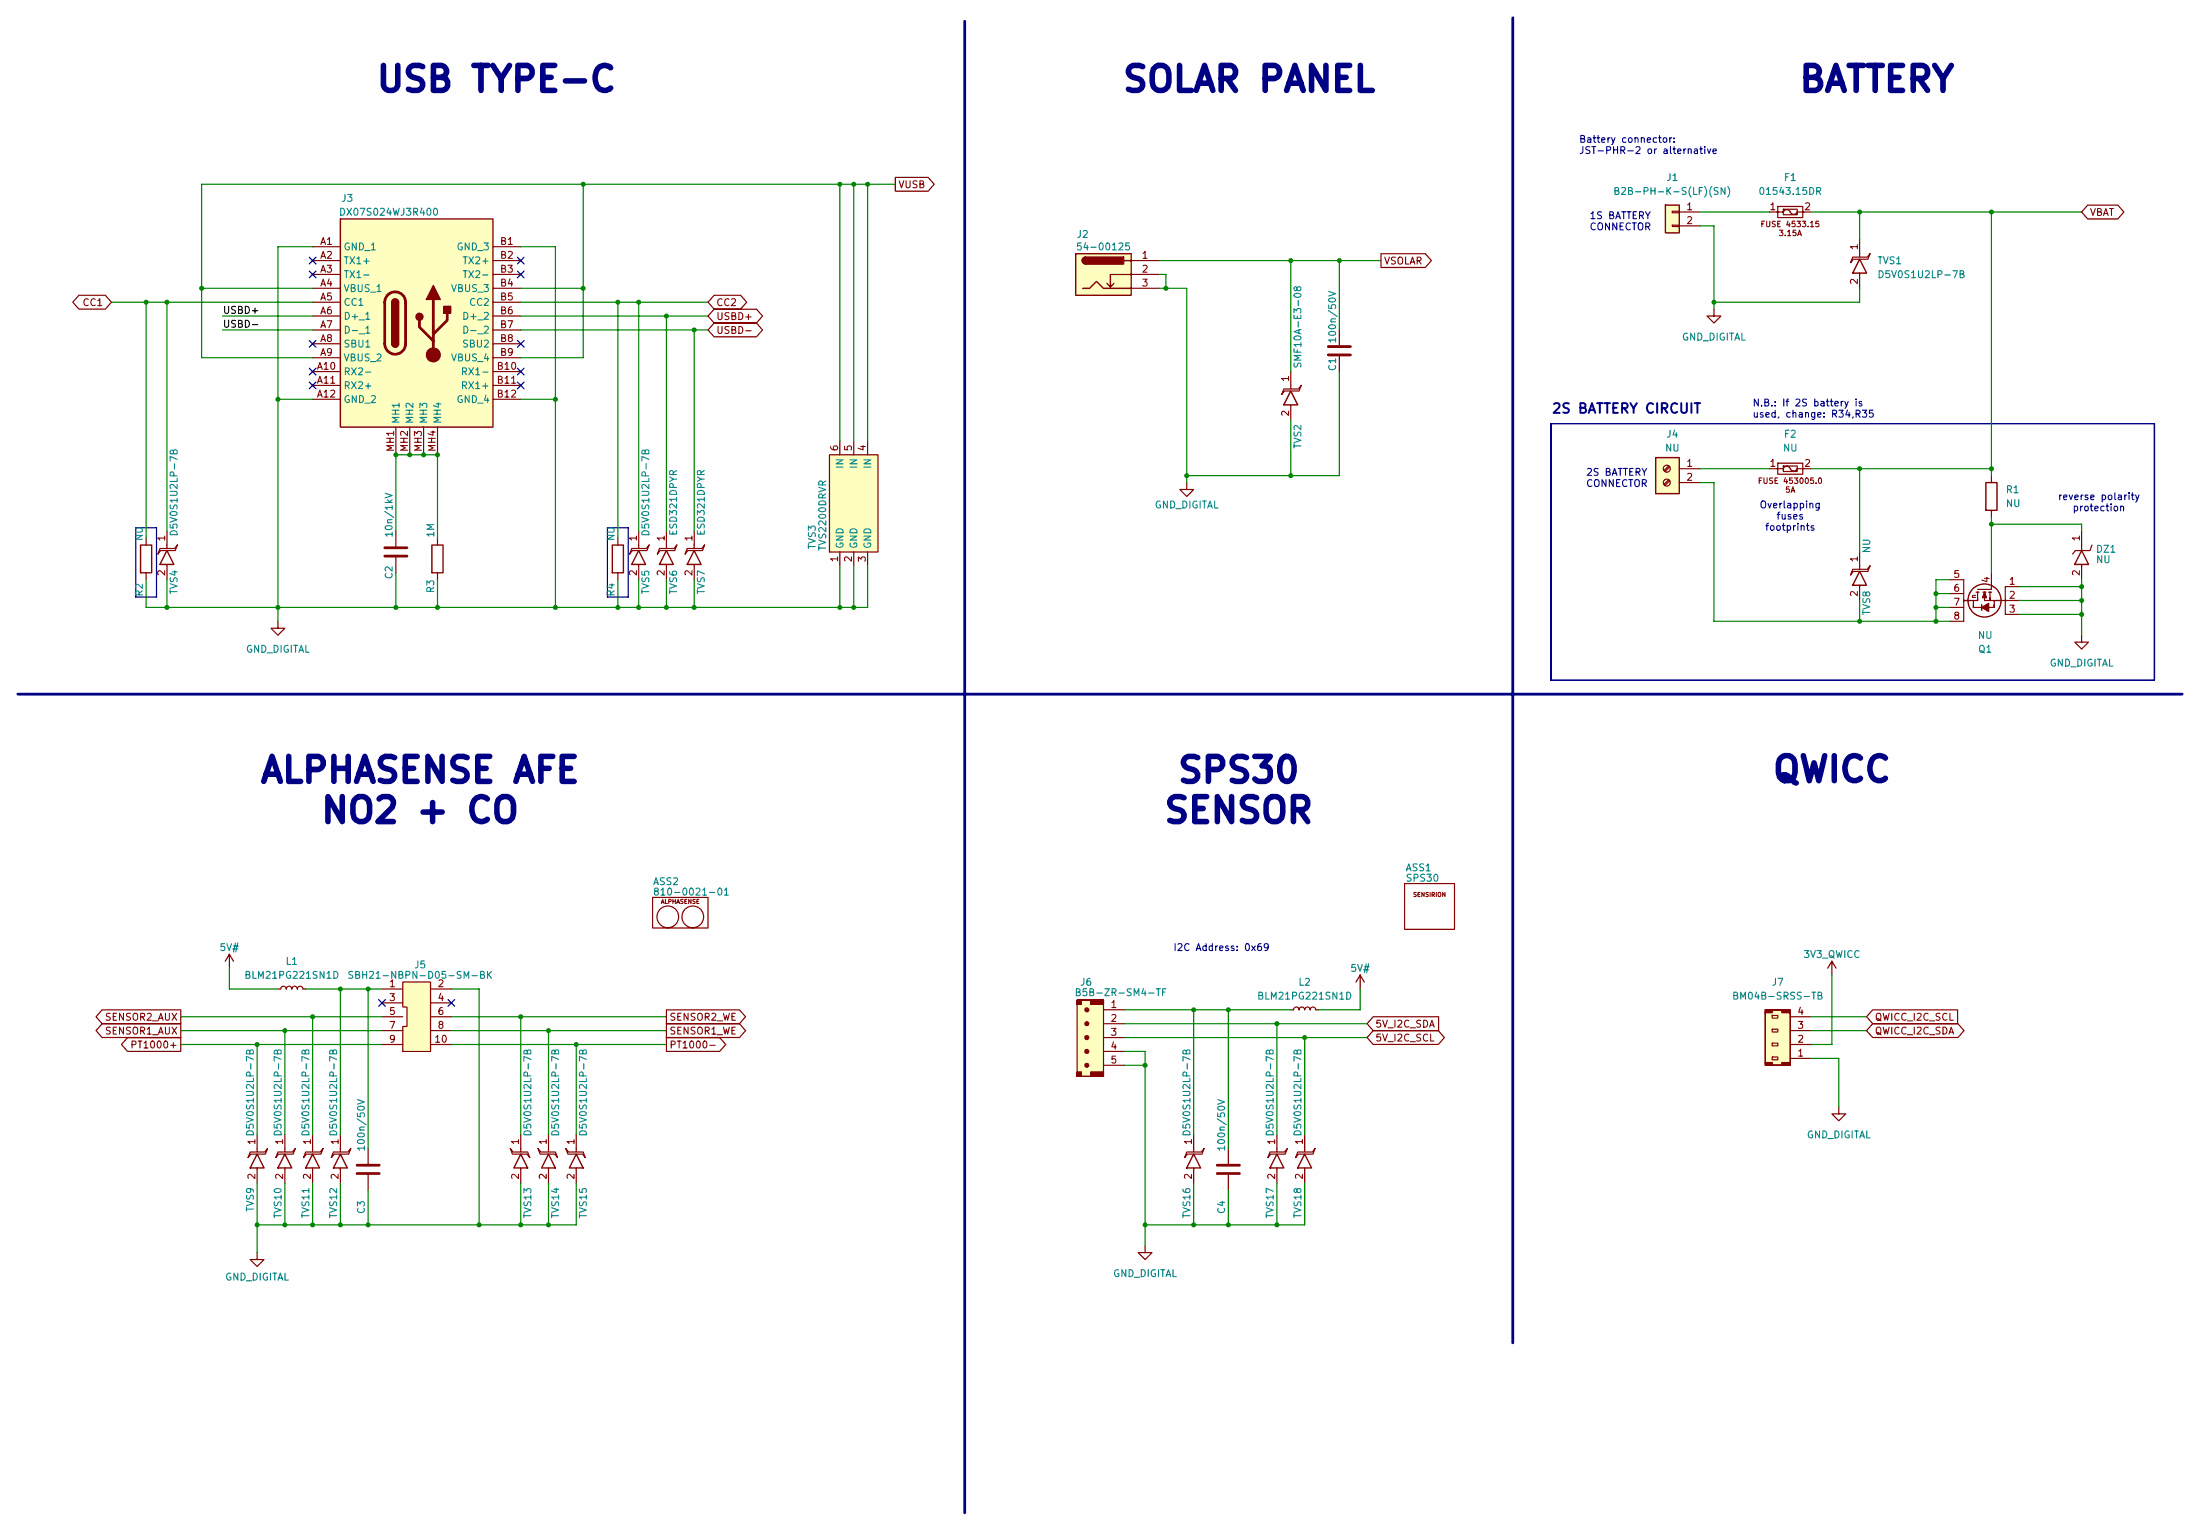
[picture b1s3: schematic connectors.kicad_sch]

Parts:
ASS1: SPS30; MPN SPS30
ASS2: 810-0021-01; MPN 810-0021-01
C1, C3, C4: 100n/50V; C_0402_1005Metric
C2: 10n/1kV; C_1206_3216Metric
DZ1: NU; D_SOD-523; MPN BZT52C12T-7
F1: 01543.15DR; 154SERIES; MPN 01543.15DR
F2: NU; 154SERIES; MPN 0154005.DR
J1: B2B-PH-K-S(LF)(SN); JST_PH_B2B-PH-K_1x02_P2.00mm_Vertical; MPN B2B-PH-K-S(LF)(SN)
J2: 54-00125; MPN 54-00125
J3: DX07S024WJ3R400; MPN DX07S024WJ3R400
J4: NU; 39543-4302; MPN 39543-4302
J5: SBH21-NBPN-D05-SM-BK; MPN SBH21-NBPN-D05-SM-BK
J6: B5B-ZR-SM4-TF; MPN B5B-ZR-SM4-TF
J7: BM04B-SRSS-TB; BM04B-SRSS_JST; MPN BM04B-SRSS-TB
L1, L2: BLM21PG221SN1D; L_0805_2012Metric; MPN BLM21PG221SN1D
Q1: NU; PowerPAK 121-8; MPN SISH402DN-T1-GE3
R1: NU; R_0402_1005Metric
R2, R4: NU; R_0603_1608Metric; MPN RC0603FR-105K1L
R3: 1M; R_1206_3216Metric
TVS1, TVS4, TVS5, TVS9, TVS10, TVS11, TVS12, TVS13, TVS14, TVS15, TVS16, TVS17, TVS18: D5V0S1U2LP-7B; D5V0S1U2LP7B; MPN M-621-D5V0S1U2LP-7B
TVS2: SMF10A-E3-08; D_SMF; MPN SMF10A-E3-08
TVS3: TVS2200DRVR; SON65P200X200X80-7N; MPN TVS2200DRVR
TVS6, TVS7: ESD321DPYR; X1SON-2; MPN ESD321DPYR
TVS8: NU; D_SMF; MPN SMF10A-E3-08

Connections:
3V3_QWICC: J7.2; also elsewhere on the board
5V#: L1.2, L2.1; also elsewhere on the board
5V_I2C_SCL: J6.3, TVS18.1; also elsewhere on the board
5V_I2C_SDA: J6.2, TVS17.1; also elsewhere on the board
CC1: J3.A5 (CC1), R2.1, TVS4.1; also elsewhere on the board
CC2: J3.B5 (CC2), R4.1, TVS5.1; also elsewhere on the board
GND_DIGITAL: C1.2, C2.2, C3.2, C4.2, DZ1.2, J1.2, J2.2, J2.3, J3.A1 (GND_1), J3.A12 (GND_2), J3.B1 (GND_3), J3.B12 (GND_4), J5.2, J6.4, J6.5, J7.1, Q1.1 (S), Q1.2 (S), Q1.3 (S), R2.2, R3.2, R4.2, TVS1.2, TVS2.2, TVS3.1 (GND), TVS3.2 (GND), TVS3.3 (GND), TVS3.7 (GND), TVS4.2, TVS5.2, TVS6.2, TVS7.2, TVS9.2, TVS10.2, TVS11.2, TVS12.2, TVS13.2, TVS14.2, TVS15.2, TVS16.2, TVS17.2, TVS18.2; also elsewhere on the board
unnamed: C2.1, J3.MH1, J3.MH2, J3.MH3, J3.MH4, R3.1
unnamed: C3.1, J5.1, L1.1, TVS12.1
unnamed: C4.1, J6.1, L2.2, TVS16.1
unnamed: F1.1, J1.1
unnamed: F2.1, J4.1
unnamed: J4.2, Q1.5 (D), Q1.6 (D), Q1.7 (D), Q1.8 (D), Q1.9 (D), TVS8.2
unnamed: DZ1.1, Q1.4 (G), R1.2
PT1000+: J5.9, TVS9.1; also elsewhere on the board
PT1000-: J5.10, TVS15.1; also elsewhere on the board
QWICC_I2C_SCL: J7.4; also elsewhere on the board
QWICC_I2C_SDA: J7.3; also elsewhere on the board
SENSOR1_AUX: J5.7, TVS10.1; also elsewhere on the board
SENSOR1_WE: J5.8, TVS14.1; also elsewhere on the board
SENSOR2_AUX: J5.5, TVS11.1; also elsewhere on the board
SENSOR2_WE: J5.6, TVS13.1; also elsewhere on the board
USBD+: J3.A6 (D+_1), J3.B6 (D+_2), TVS6.1; also elsewhere on the board
USBD-: J3.A7 (D-_1), J3.B7 (D-_2), TVS7.1; also elsewhere on the board
VBAT: F1.2, F2.2, R1.1, TVS1.1, TVS8.1; also elsewhere on the board
VSOLAR: C1.1, J2.1, TVS2.1; also elsewhere on the board
VUSB: J3.A4 (VBUS_1), J3.A9 (VBUS_2), J3.B4 (VBUS_3), J3.B9 (VBUS_4), TVS3.4 (IN), TVS3.5 (IN), TVS3.6 (IN); also elsewhere on the board

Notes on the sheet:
SPS30 SENSOR
1S BATTERY CONNECTOR
Overlapping fuses footprints
Battery connector: JST-PHR-2 or alternative
QWICC
reverse polarity protection
BATTERY
SOLAR PANEL
USB TYPE-C
2S BATTERY CONNECTOR
N.B.: If 2S battery is used, change: R34,R35
ALPHASENSE AFE NO2 + CO
2S BATTERY CIRCUIT
I2C Address: 0x69

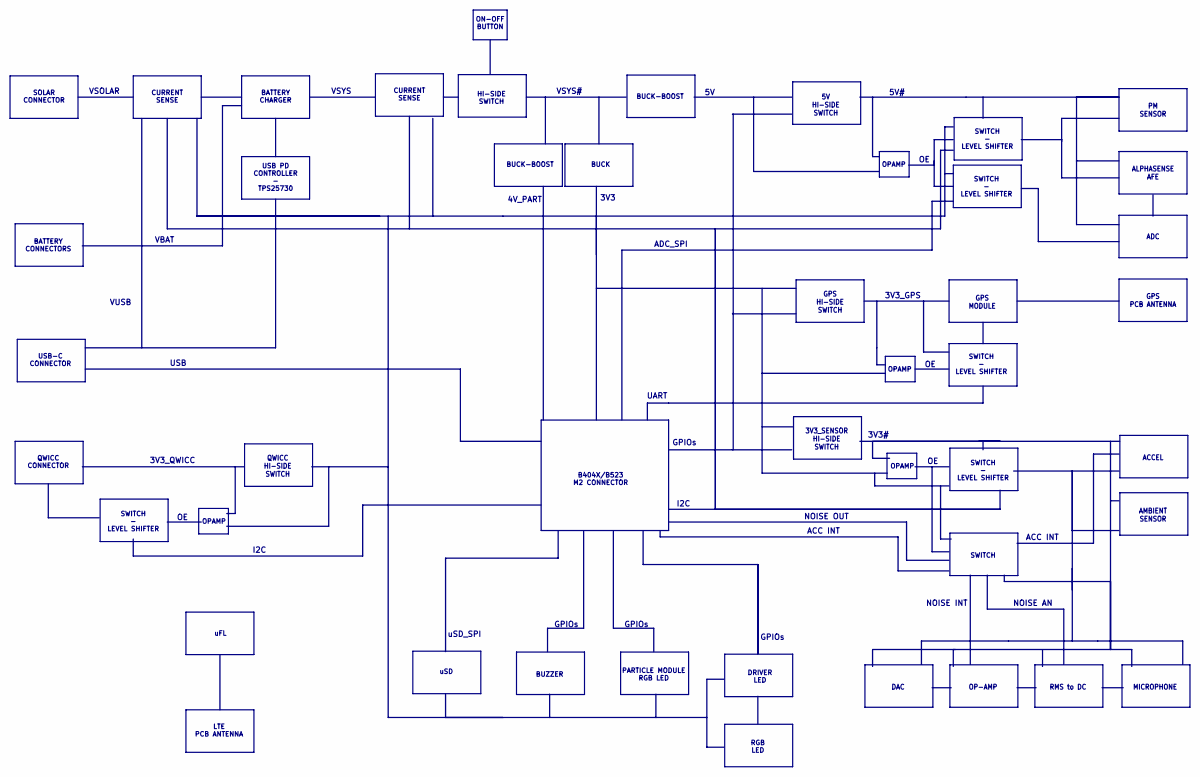
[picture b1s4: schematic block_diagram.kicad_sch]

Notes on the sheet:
GPIOs
SOLAR CONNECTOR
PARTICLE MODULE RGB LED
USB
uSD_SPI
RGB LED
QWICC CONNECTOR
MICROPHONE
OP-AMP
ACC INT
DAC
BATTERY CHARGER
4V_PART
3V3_GPS
GPIOs
SWITCH - LEVEL SHIFTER
3V3_QWICC
NOISE AN
3V3#
NOISE INT
VUSB
VSYS#
5V HI-SIDE SWITCH
ON-OFF BUTTON
5V#
3V3
OPAMP
CURRENT SENSE
QWICC HI-SIDE SWITCH
LTE PCB ANTENNA
BUCK
PM SENSOR
BATTERY CONNECTORS
uSD
3V3_SENSOR HI-SIDE SWITCH
VBAT
USB-C CONNECTOR
DRIVER LED
SWITCH
uFL

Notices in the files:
README.md:
Todos os materiais estão sob a licença [MIT License](LICENSE).
